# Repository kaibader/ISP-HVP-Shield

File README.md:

# ISP-HVP-Shield

Arduino ISP and HVSP/HVPP Shield for ATtiny Microcontoller

## Preface

**This repository is discontinued and only provided for others to further work
with its content.**

Eagle CAD version 7 was used to create the schematic and board files. The latest
version I've tested was Eagle CAD v7.7. I do not support the price and product
policy of Autodesk and therefore have moved from Eagle CAD to the free and open
source KiCad. I can only recommend you to do the same.

## Version 1.0

This is the original version of the Arduino ISP shield which not only has been
successfully tested but also copied/created by various other users.

**If you are unsure which version to use for further experiments stick to this
one.**

## Version 1.1

This was a slightly improved version of the original ATtiny ISP Shield.
This version was *never produced and never tested* as real hardware.

## Version 2.0

This was an experimental version which not only should allow the programming
of ATtiny microcontollers but also erase their fuses (via high voltage
programming).

The TopoR autorouter was used to route the v2.0 board which then was used to
generate the Gerber files. I've added an ripped-up version of the board for
compatibility reasons.

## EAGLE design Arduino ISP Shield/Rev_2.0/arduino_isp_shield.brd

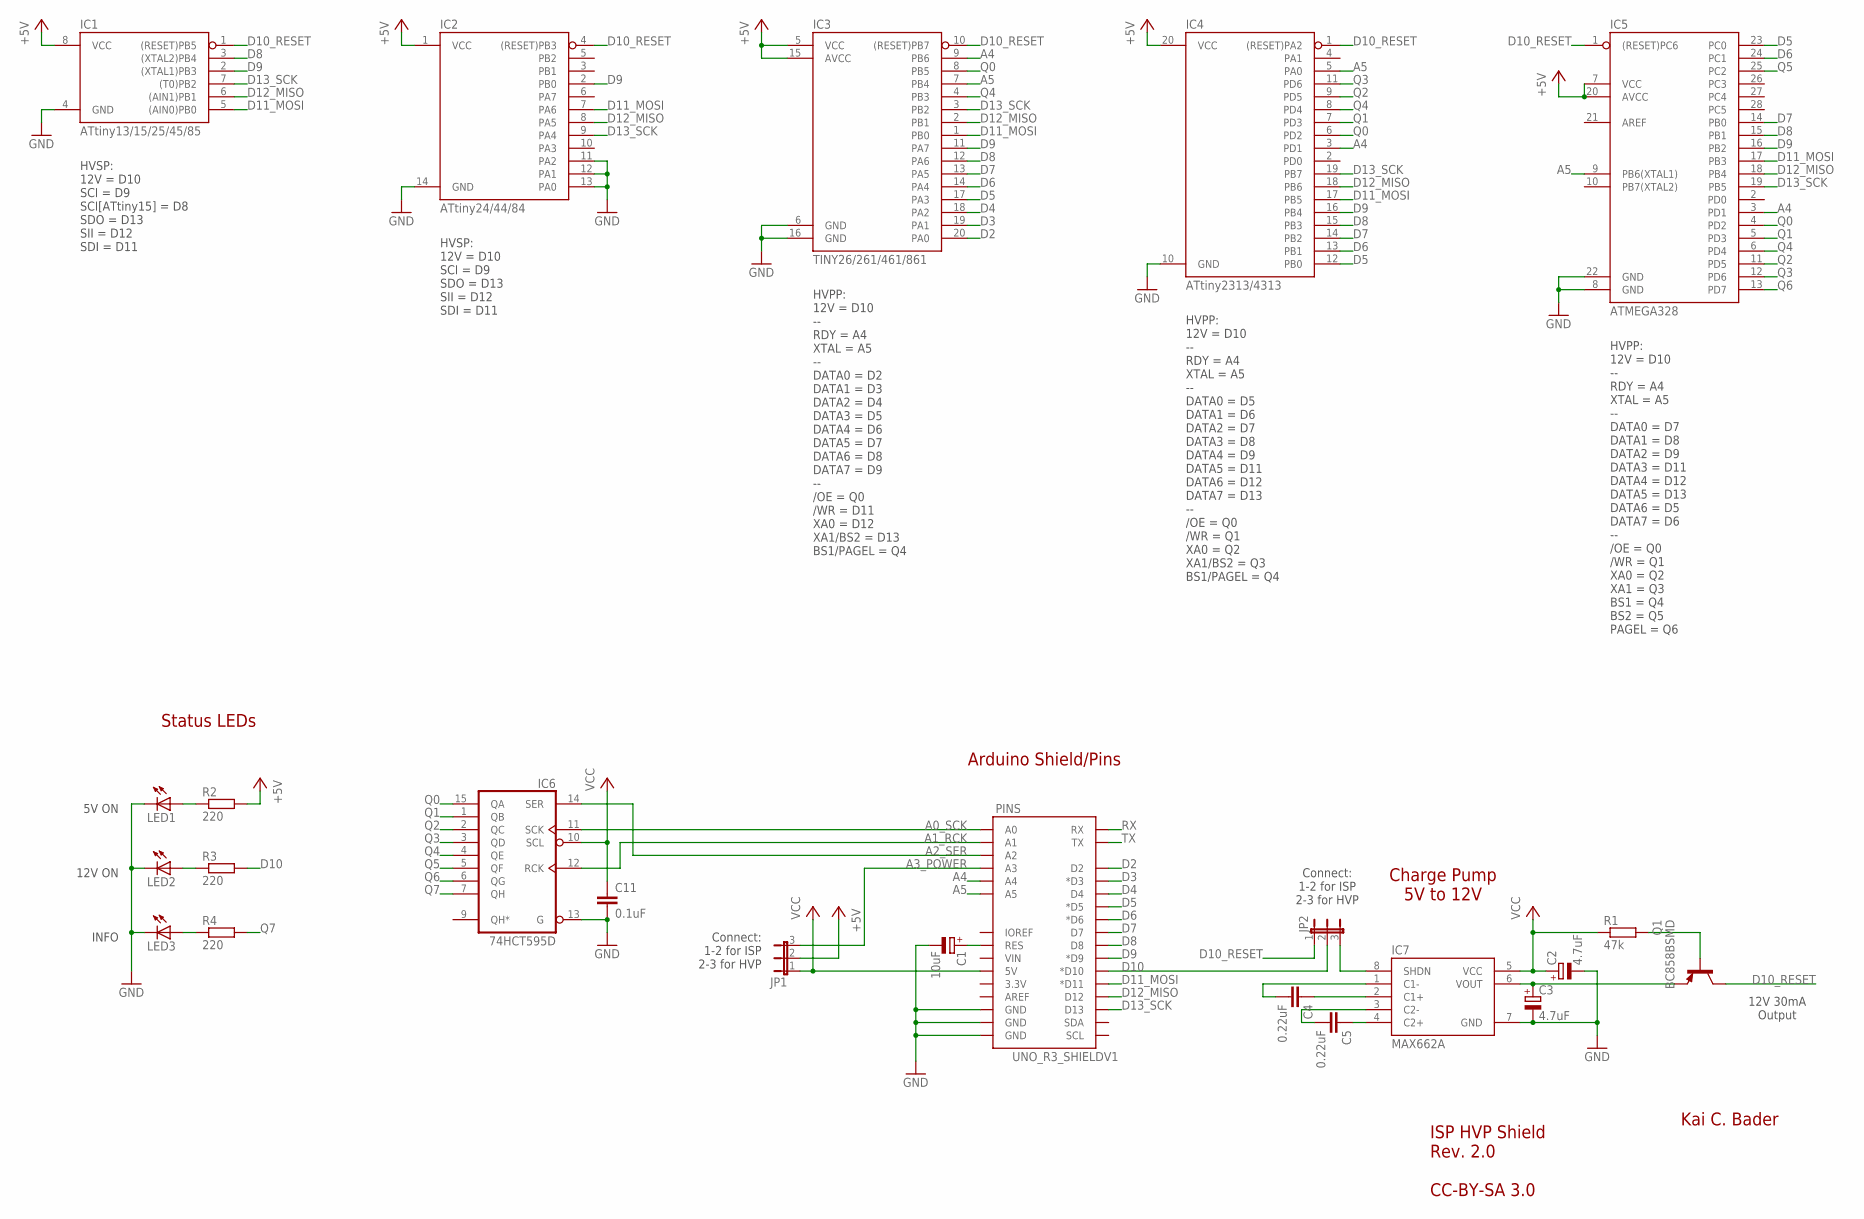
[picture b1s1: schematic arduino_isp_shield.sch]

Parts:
C1: 10uF; E2-5
C2, C3: 4.7uF; E2-5
C4, C5: 0.22uF; C0805
C11: 0.1uF; C0805
IC1: ATtiny13/15/25/45/85; DIL08
IC2: ATtiny24/44/84; DIL14
IC3: TINY26/261/461/861; DIL20
IC4: ATtiny2313/4313; DIL20
IC5: ATMEGA328; DIL28
IC6: 74HCT595D; SO16
IC7: MAX662A; SO08
JP1, JP2: JP2E; JP2
LED1, LED2, LED3: LEDCHIPLED_0805; CHIPLED_0805
PINS: UNO_R3_SHIELDV1; UNO_R3_SHIELD
Q1: BC858BSMD; SOT23-BEC
R1: 47k; R0805
R2, R3, R4: 220; R0805

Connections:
220: LED2.A, R3.1
+5V: IC1.8 (VCC), IC2.1 (VCC), IC3.5 (VCC), IC3.15 (AVCC), IC4.20 (VCC), IC5.7 (VCC), IC5.20 (AVCC), JP1.2, R2.2
A0_SCK: IC6.11 (SCK), PINS.A0
A1_RCK: IC6.12 (RCK), PINS.A1
A2_SER: IC6.14 (SER), PINS.A2
A3_POWER: JP1.3, PINS.A3
A4: IC3.9 (PB6), IC4.3 (PD1), IC5.3 (PD1), PINS.A4
A5: IC3.7 (PB4), IC4.5 (PA0), IC5.9 (PB6(XTAL1)), PINS.A5
AREF: IC5.21 (AREF)
D2: IC3.20 (PA0), PINS.D2
D3: IC3.19 (PA1), PINS.D3 (*D3)
D4: IC3.18 (PA2), PINS.D4
D5: IC3.17 (PA3), IC4.12 (PB0), IC5.23 (PC0), PINS.D5 (*D5)
D6: IC3.14 (PA4), IC4.13 (PB1), IC5.24 (PC1), PINS.D6 (*D6)
D7: IC3.13 (PA5), IC4.14 (PB2), IC5.14 (PB0), PINS.D7
D8: IC1.3 ((XTAL2)PB4), IC3.12 (PA6), IC4.15 (PB3), IC5.15 (PB1), PINS.D8
D9: IC1.2 ((XTAL1)PB3), IC2.2 (PB0), IC3.11 (PA7), IC4.16 (PB4), IC5.16 (PB2), PINS.D9 (*D9)
D10: JP2.2, PINS.D10 (*D10), R3.2
D10_RESET: IC1.1 ((RESET)PB5), IC2.4 ((RESET)PB3), IC3.10 ((RESET)PB7), IC4.1 ((RESET)PA2), IC5.1 ((RESET)PC6), JP2.1, Q1.C
D11_MOSI: IC1.5 ((AIN0)PB0), IC2.7 (PA6), IC3.1 (PB0), IC4.17 (PB5), IC5.17 (PB3), PINS.D11 (*D11)
D12_MISO: IC1.6 ((AIN1)PB1), IC2.8 (PA5), IC3.2 (PB1), IC4.18 (PB6), IC5.18 (PB4), PINS.D12
D13_SCK: IC1.7 ((T0)PB2), IC2.9 (PA4), IC3.3 (PB2), IC4.19 (PB7), IC5.19 (PB5), PINS.D13
GND: C1.-, C2.-, C3.-, C11.2, IC1.4 (GND), IC2.11 (PA2), IC2.12 (PA1), IC2.13 (PA0), IC2.14 (GND), IC3.6 (GND), IC3.16 (GND), IC4.10 (GND), IC5.8 (GND), IC5.22 (GND), IC6.8 (GND), IC6.13 (G), IC7.7 (GND), LED1.C, LED2.C, LED3.C, PINS.GND@0 (GND), PINS.GND@1 (GND), PINS.GND@2 (GND)
unnamed: IC7.8 (SHDN), JP2.3
unnamed: C1.+, PINS.RES
unnamed: Q1.B, R1.2
unnamed: C5.1, IC7.4 (C2+)
unnamed: C5.2, IC7.3 (C2-)
unnamed: C4.1, IC7.2 (C1+)
unnamed: C4.2, IC7.1 (C1-)
unnamed: LED1.A, R2.1
unnamed: LED3.A, R4.1
Q0: IC3.8 (PB5), IC4.6 (PD2), IC5.4 (PD2), IC6.15 (QA)
Q1: IC4.7 (PD3), IC5.5 (PD3), IC6.1 (QB)
Q2: IC4.9 (PD5), IC5.11 (PD5), IC6.2 (QC)
Q3: IC4.11 (PD6), IC5.12 (PD6), IC6.3 (QD)
Q4: IC3.4 (PB3), IC4.8 (PD4), IC5.6 (PD4), IC6.4 (QE)
Q5: IC5.25 (PC2), IC6.5 (QF)
Q6: IC5.13 (PD7), IC6.6 (QG)
Q7: IC6.7 (QH), R4.2
RX: PINS.RX
TX: PINS.TX
VCC: C2.+, C11.1, IC6.10 (SCL), IC6.16 (VCC), IC7.5 (VCC), JP1.1, PINS.5V, R1.1
VOUT: C3.+, IC7.6 (VOUT), Q1.E

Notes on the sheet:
Kai C. Bader
ISP HVP Shield Rev. 2.0 CC-BY-SA 3.0
Charge Pump 5V to 12V
Arduino Shield/Pins
HVSP: 12V = D10 SCI = D9 SCI[ATtiny15] = D8 SDO = D13 SII = D12 SDI = D11
HVSP: 12V = D10 SCI = D9 SDO = D13 SII = D12 SDI = D11
HVPP: 12V = D10 -- RDY = A4 XTAL = A5 -- DATA0 = D5 DATA1 = D6 DATA2 = D7 DATA3 = D8 DATA4 = D9 DATA5 = D11 DATA6 = D12 DATA7 = D13 -- /OE = Q0 /WR = Q1 XA0 = Q2 XA1/BS2 = Q3 BS1/PAGEL = Q4
Connect: 1-2 for ISP 2-3 for HVP
HVPP: 12V = D10 -- RDY = A4 XTAL = A5 -- DATA0 = D2 DATA1 = D3 DATA2 = D4 DATA3 = D5 DATA4 = D6 DATA5 = D7 DATA6 = D8 DATA7 = D9 -- /OE = Q0 /WR = D11 XA0 = D12 XA1/BS2 = D13 BS1/PAGEL = Q4
HVPP: 12V = D10 -- RDY = A4 XTAL = A5 -- DATA0 = D7 DATA1 = D8 DATA2 = D9 DATA3 = D11 DATA4 = D12 DATA5 = D13 DATA6 = D5 DATA7 = D6 -- /OE = Q0 /WR = Q1 XA0 = Q2 XA1 = Q3 BS1 = Q4 BS2 = Q5 PAGEL = Q6
12V 30mA Output
Status LEDs
5V ON
12V ON
INFO

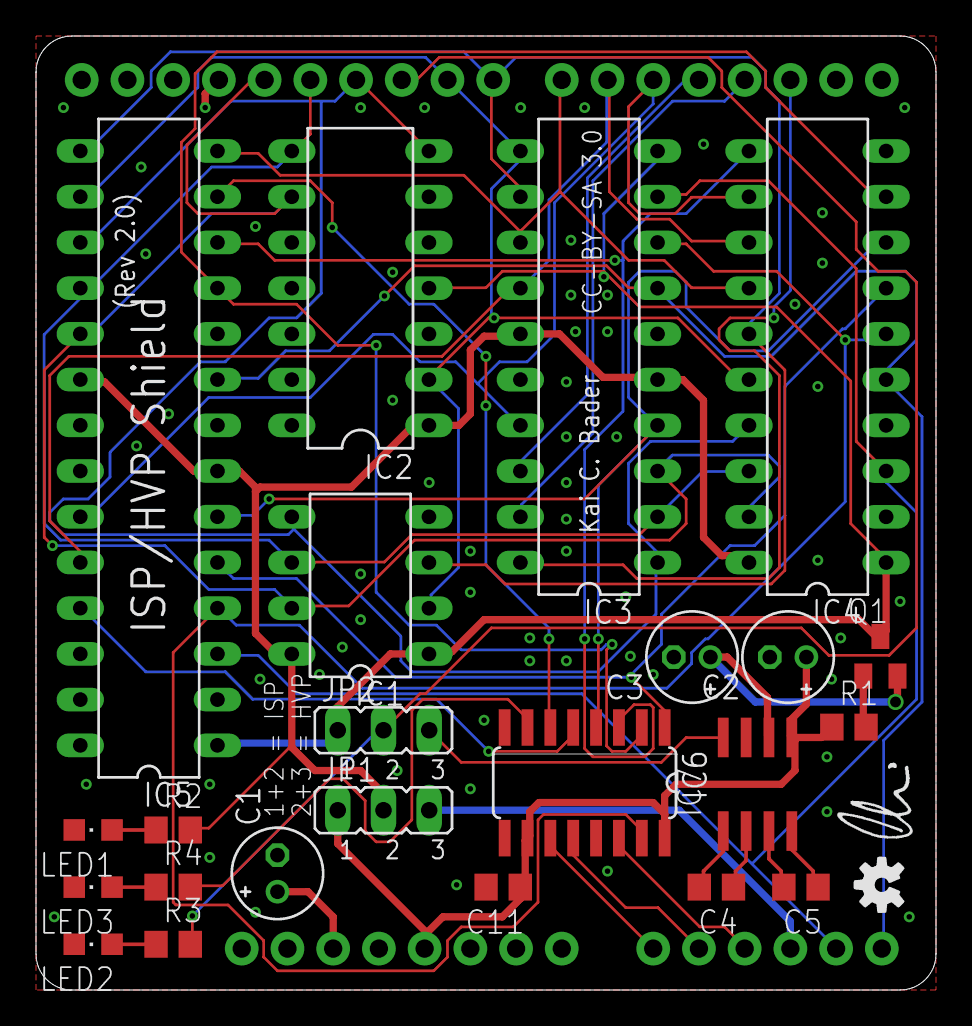
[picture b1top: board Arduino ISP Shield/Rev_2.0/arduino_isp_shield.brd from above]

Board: 2 copper layers, 50.0 x 53.0 mm, 26 parts (0 on the bottom side), 41 nets.

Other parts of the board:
U$1: OSHW-LOGO-S
U$3: KAI-LOGO-M

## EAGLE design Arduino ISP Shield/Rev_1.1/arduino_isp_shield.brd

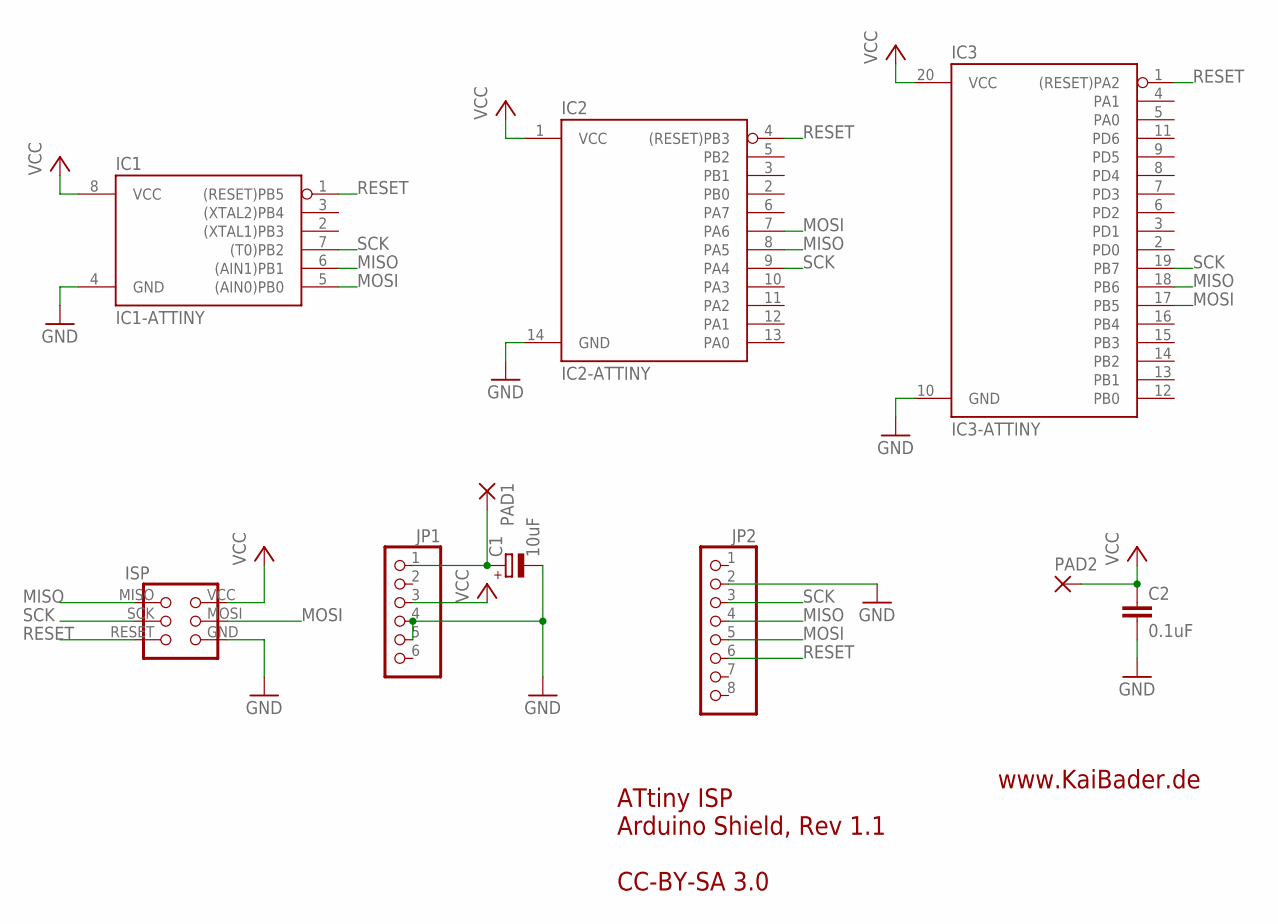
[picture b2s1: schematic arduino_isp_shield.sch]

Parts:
C1: 10uF; E1,8-4
C2: 0.1uF; C050-025X075
IC1: IC1-ATTINY; DIL08
IC2: IC2-ATTINY; DIL14
IC3: IC3-ATTINY; DIL20
ISP: AVR-ISP
JP1: PINHD-1X6; 1X06
JP2: PINHD-1X8; 1X08
PAD1, PAD2: 1,6/0,8

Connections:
GND: C1.-, C2.2, IC1.4 (GND), IC2.14 (GND), IC3.10 (GND), ISP.GND, JP1.4, JP1.5, JP2.2
MISO: IC1.6 ((AIN1)PB1), IC2.8 (PA5), IC3.18 (PB6), ISP.MISO, JP2.4
MOSI: IC1.5 ((AIN0)PB0), IC2.7 (PA6), IC3.17 (PB5), ISP.MOSI, JP2.5
unnamed: C1.+, JP1.1, PAD1.1
RESET: IC1.1 ((RESET)PB5), IC2.4 ((RESET)PB3), IC3.1 ((RESET)PA2), ISP.RESET, JP2.6
SCK: IC1.7 ((T0)PB2), IC2.9 (PA4), IC3.19 (PB7), ISP.SCK, JP2.3
VCC: C2.1, IC1.8 (VCC), IC2.1 (VCC), IC3.20 (VCC), ISP.VCC, JP1.3, PAD2.1

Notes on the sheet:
www.KaiBader.de
ATtiny ISP Arduino Shield, Rev 1.1 CC-BY-SA 3.0

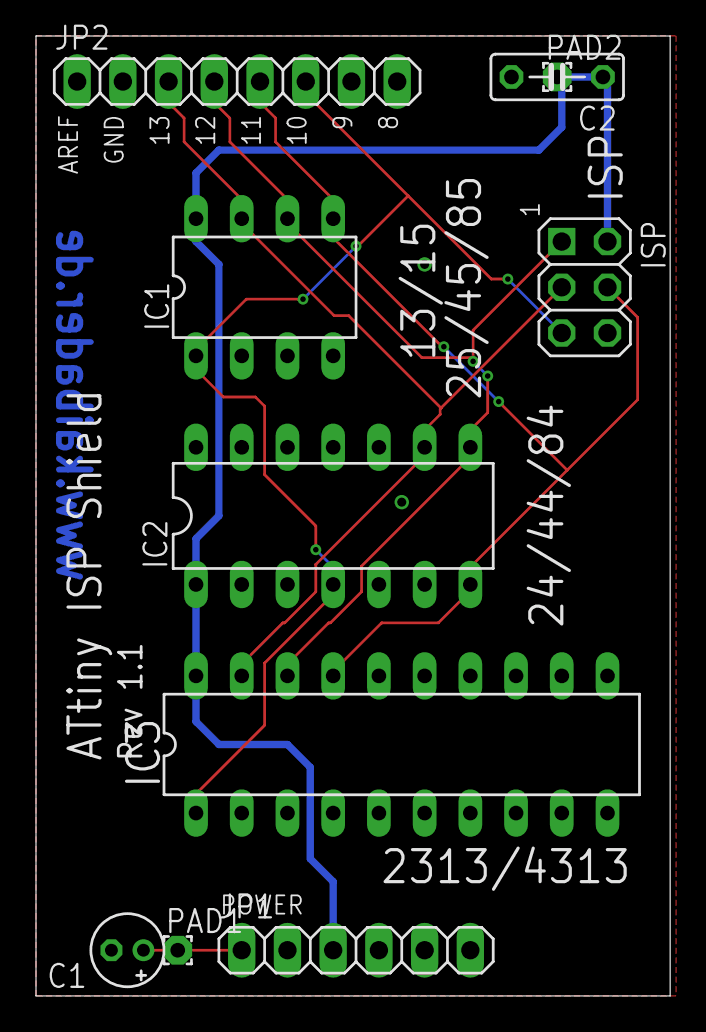
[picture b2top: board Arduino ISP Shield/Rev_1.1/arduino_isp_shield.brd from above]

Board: 2 copper layers, 35.2 x 53.3 mm, 10 parts (0 on the bottom side), 7 nets.

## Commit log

2013-10-22 Initial commit (ignore list). This is a repository of my Eagle CAD files.
2013-10-22 Added new files. May need to be cleaned up later...
2015-03-19 New design. Started to add HVSP/HVPP features.
2015-03-20 Added test board 'optimized' with topor.
2015-03-21 Added Gerber files.
2015-03-21 Sent Gerber files to fab house...
2015-03-26 Some clean-up.
2015-04-19 A little bit of housecleaning...
2015-04-25 More cleaning...
2017-04-13 Fixed the forward<->backward compatibility.
    - Ripped up the board file to fix the schematic board compatibility.
    - Moved the TopoR (auto)routed board to a different location.
2017-04-13 Created a README.md comment
2018-02-13 Updated the Ignore List
2018-02-14 New Revision 1.1 Board designed with KiCad
    This board is identical to Revision 1.0 besides two instead of one
    decoupling capacitor and a new layout.
2018-02-15 Minor adaptions: improved the alignment of some traces.
2018-02-15 Minor fix due to DRC warning
2018-02-15 Renamed the Gerber files
2018-02-15 Minor Silk Screen Fix
2018-06-12 Renamed 'Revision_*' into 'Version_*'... avoids confusion.
